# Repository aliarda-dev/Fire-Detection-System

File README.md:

🔥 Smart Fire Detection System

Bu proje, sıcaklık ve gaz sensörlerinden alınan verileri birlikte değerlendirerek yangın riskini tespit eden basit bir gömülü sistem prototipidir.

🛠️ Donanım

* Arduino Uno
* DHT11 (sıcaklık sensörü)
* MQ-2 (gaz/duman sensörü)
* Buzzer
* Kırmızı LED

⚙️ Nasıl Çalışır?

* DHT11 ile sıcaklık, MQ-2 ile gaz yoğunluğu okunur
* Sensör verileri belirlenen eşik değerlerle karşılaştırılır

Sistem iki farklı durumda çalışır:

**1. Gaz Sızıntısı (Uyarı Modu)**

* Sadece gaz değeri threshold'u aşarsa
* LED yakılır (sessiz uyarı)

**2. Yangın (Alarm Modu)**

* Hem sıcaklık hem gaz değeri eşik üstündeyse

* LED + buzzer aktif olur

* Sensör verileri UART (Serial) üzerinden anlık olarak izlenebilir

📖 Teknik Notlar

* Basit bir sensor fusion mantığı kullanıldı (AND koşulu)
* Karar mekanizması if-else yapısı ile kuruldu
* Sistem deterministik ve hızlı tepki verecek şekilde tasarlandı

⚠️ Limitasyonlar

* Sensörler kalibre edilmediği için ölçümler hassas değildir
* Sabit threshold kullanıldığı için ortam koşullarına adaptif değildir

💡 Geliştirme Fikirleri

* Adaptive threshold
* Sensör kalibrasyonu
* ESP8266 ile uzaktan bildirim (IoT entegrasyonu)
* Röle ile otomatik müdahale sistemi

***Not*** 

Projenin pil kaynaklı,switch kullanılarak yapılacak halinin pcb tasarımı ve gerekli gerber dosyaları yüklendi.

🎥 Proje Demo

Projenin çalışma videosunu aşağıdan izleyebilirsiniz.

https://github.com/user-attachments/assets/633bbb7a-b0dc-49af-93b6-7b49733193ba

📷 Proje PCB Medyası

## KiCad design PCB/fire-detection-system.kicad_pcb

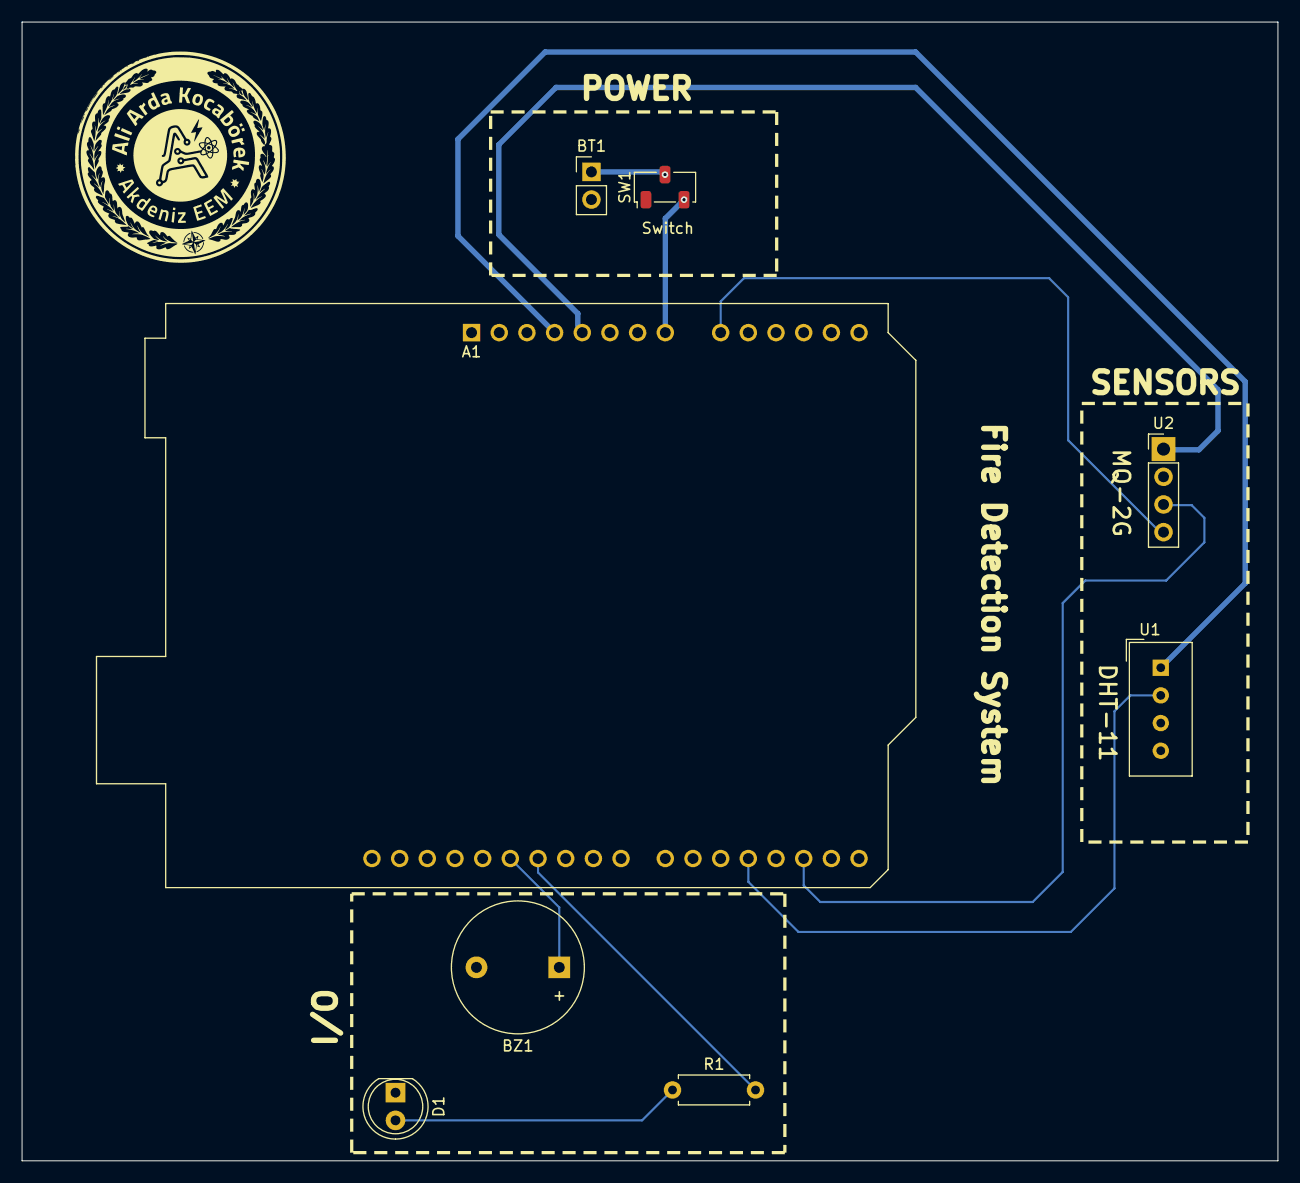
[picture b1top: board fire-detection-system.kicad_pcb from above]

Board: 2 copper layers, 115.2 x 104.5 mm, 8 parts (0 on the bottom side), 11 nets.

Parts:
A1: Arduino_UNO_R3
BT1: 9V; PinHeader_1x02_P2.54mm_Vertical
BZ1: Buzzer; Buzzer_12x9.5RM7.6
D1: LED; LED_D5.0mm
R1: 330R; R_Axial_DIN0207_L6.3mm_D2.5mm_P7.62mm_Horizontal
SW1: SW_Nidec_CAS-120A1; Nidec_Copal_CAS-120A
U1: DHT11; Aosong_DHT11_5.5x12.0_P2.54mm
U2: mq2-gas-sensor

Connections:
3.3V: A1.4 (3V3), U1.1 (VDD)
5V: A1.5 (+5V), U2.1 (VCC)
A0-MQ2: A1.9 (A0), U2.4 (AO)
BO: A1.27 (D12), BZ1.1 (+)
DATA-STH11: A1.19 (D4), U1.2 (DATA)
DO-MQ2: A1.17 (D2), U2.3 (DO)
GND: A1.6 (GND), A1.7 (GND), A1.29 (GND), BT1.2 (-), BZ1.2 (-), D1.1 (K), U1.4 (GND), U2.2 (GND)
LED: A1.26 (D11), R1.2
unnamed: BT1.1 (+), SW1.2 (B)
unnamed: D1.2 (A), R1.1
VCC: A1.8 (VIN), SW1.3 (A)

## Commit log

2026-06-17 About Fire Detection System
2026-06-17 Added Media
2026-06-22 Arduino IDE Code For Fire Detection System
2026-06-26 Create dd
2026-06-26 Create da
2026-06-26 PCB Files for This Project
2026-06-27 About Fire Detection System
    Added note about battery-powered version and PCB design.
2026-06-28 Added Gerber Files
2026-06-28 Added PCB Files
2026-06-28 Production Zip Added
